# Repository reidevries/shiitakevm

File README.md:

# shiitakevm
CV-addressed multiplexor with interpolation, either for arbitrary waveshaping or crossfading ext sources
I never tested this, but have a new version in the pipeline that will hopefully be better when I test it.

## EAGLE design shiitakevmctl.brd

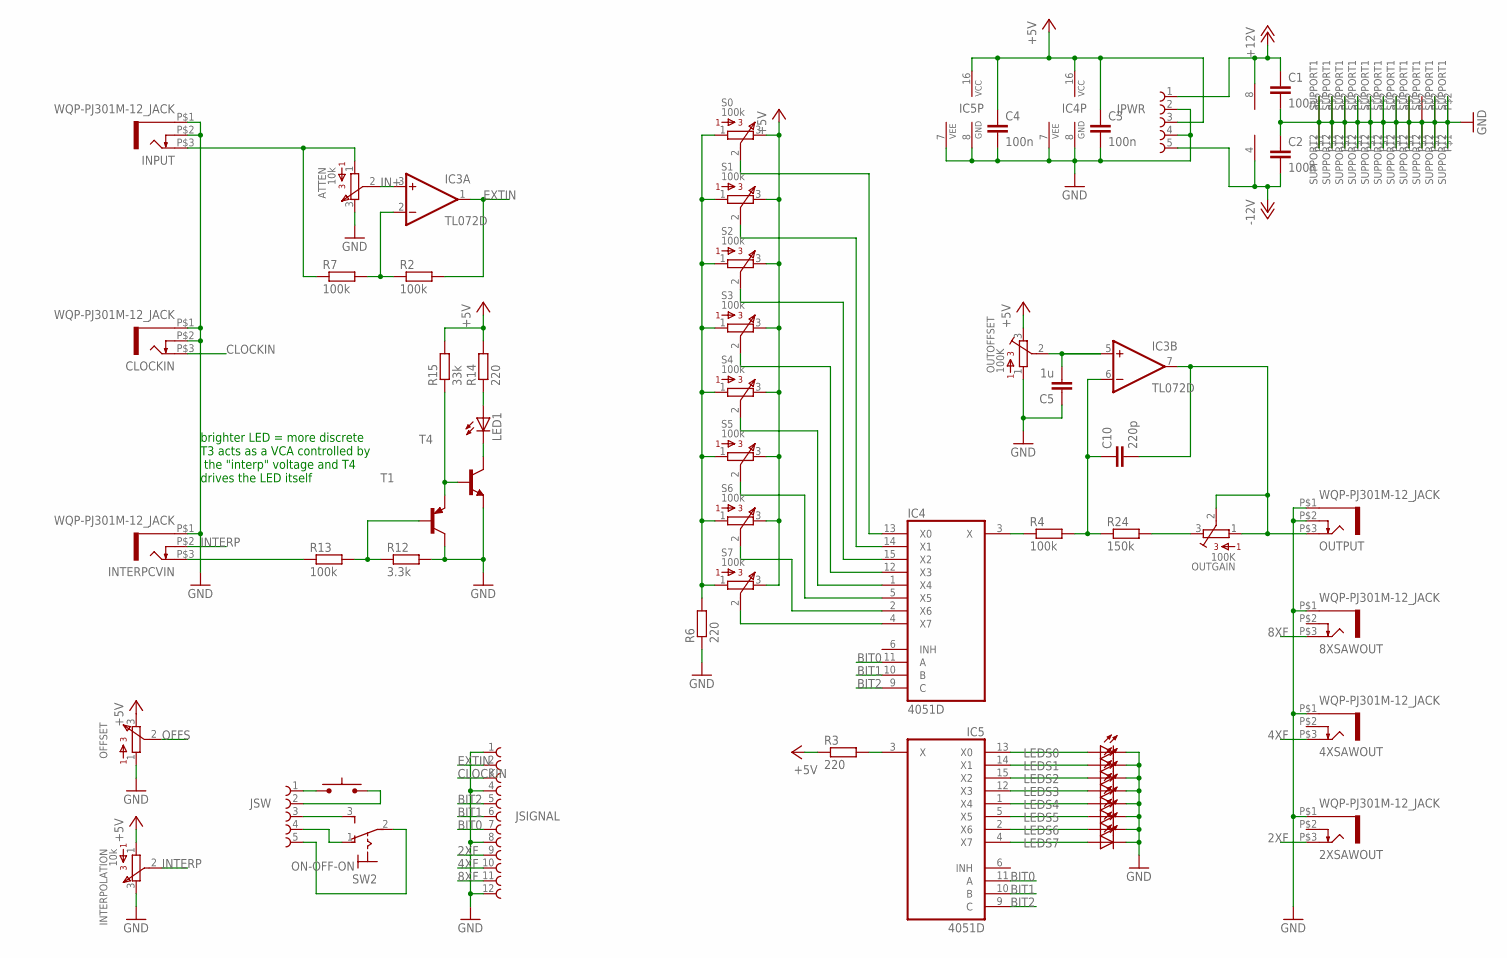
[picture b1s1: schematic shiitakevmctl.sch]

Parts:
2XSAWOUT, 4XSAWOUT, 8XSAWOUT: WQP-PJ301M-12_JACK
ATTEN: 10k; 308
C1, C2, C3, C4: 100n; C1206
C5: 1u; C1206
C10: 220p; C1206
CLOCKIN: WQP-PJ301M-12_JACK
IC3: TL072D; SO08
IC4, IC5: 4051D; SO16
INPUT: WQP-PJ301M-12_JACK
INTERPCVIN: WQP-PJ301M-12_JACK
INTERPOLATION: 10k; 308
JPWR: 61300511121
JSIGNAL: 61301211121
JSW: 61300511121
LED1: LEDCHIPLED_0805; CHIPLED_0805
LEDS0, LEDS1, LEDS2, LEDS3, LEDS4, LEDS5, LEDS6, LEDS7: LED3MM
OFFSET: 308/309; 308
OUTGAIN: 100K; 3386C
OUTOFFSET: 100K; 3386C
OUTPUT: WQP-PJ301M-12_JACK
R2, R4, R7, R13: 100k; R1206
R3, R6, R14: 220; R1206
R12: 3.3k; R1206
R15: 33k; R1206
R24: 150k; R1206
S0, S1, S2, S3, S4, S5, S6, S7: 100k; 308
SW1: PUSHSWITCH
SW2: ON-OFF-ON; 320-916
T1: MMBT3906LT1-PNP-SOT23-BEC; SOT23-BEC
T4: MMBT3904LT1-NPN-SOT23-BEC; SOT23-BEC

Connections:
2XF: 2XSAWOUT.P$3 (2), JSIGNAL.9
4XF: 4XSAWOUT.P$3 (2), JSIGNAL.10
8XF: 8XSAWOUT.P$3 (2), JSIGNAL.11
+5V: C3.1, C4.1, IC4.16 (VCC), IC5.16 (VCC), INTERPOLATION.1, JPWR.3, OFFSET.3, OUTOFFSET.3, R3.1, R14.2, R15.2, S0.3, S1.3, S2.3, S3.3, S4.3, S5.3, S6.3, S7.3
+12V: C1.1, IC3.8 (V+), JPWR.1
-12V: C2.2, IC3.4 (V-), JPWR.5
BIT0: IC4.11 (A), IC5.11 (A), JSIGNAL.7
BIT1: IC4.10 (B), IC5.10 (B), JSIGNAL.6
BIT2: IC4.9 (C), IC5.9 (C), JSIGNAL.5
CLOCKIN: CLOCKIN.P$3 (2), JSIGNAL.3
EXTIN: IC3.1 (OUT), JSIGNAL.2, R2.2
GND: 2XSAWOUT.P$1 (1), 4XSAWOUT.P$1 (1), 8XSAWOUT.P$1 (1), ATTEN.3, ATTEN.SUPPORT2, C1.2, C2.1, C3.2, C4.2, C5.1, CLOCKIN.P$1 (1), CLOCKIN.P$2 (3), IC4.7 (VEE), IC4.8 (GND), IC5.7 (VEE), IC5.8 (GND), INPUT.P$1 (1), INPUT.P$2 (3), INTERPCVIN.P$1 (1), INTERPOLATION.3, INTERPOLATION.SUPPORT1, INTERPOLATION.SUPPORT2, JPWR.2, JPWR.4, JSIGNAL.1, JSIGNAL.4, JSIGNAL.8, JSIGNAL.12, LEDS0.K (C), LEDS1.K (C), LEDS2.K (C), LEDS3.K (C), LEDS4.K (C), LEDS5.K (C), LEDS6.K (C), LEDS7.K (C), OFFSET.1, OFFSET.SUPPORT1, OFFSET.SUPPORT2, OUTOFFSET.1, OUTPUT.P$1 (1), OUTPUT.P$2 (3), R6.1, R12.2, S0.SUPPORT1, S0.SUPPORT2, S1.SUPPORT1, S1.SUPPORT2, S2.SUPPORT1, S2.SUPPORT2, S3.SUPPORT1, S3.SUPPORT2, S4.SUPPORT1, S4.SUPPORT2, S5.SUPPORT1, S5.SUPPORT2, S6.SUPPORT1, S6.SUPPORT2, S7.SUPPORT1, S7.SUPPORT2, T1.C, T4.E
IN+: ATTEN.2, IC3.3 (+IN)
INTERP: INTERPCVIN.P$2 (3), INTERPOLATION.2
unnamed: C10.1, IC3.6 (-IN), R4.2, R24.1
unnamed: C10.2, IC3.7 (OUT), OUTGAIN.1, OUTGAIN.2, OUTPUT.P$3 (2)
unnamed: ATTEN.1, INPUT.P$3 (2), R7.1
unnamed: IC4.13 (X0), S0.2
unnamed: IC4.14 (X1), S1.2
unnamed: IC4.15 (X2), S2.2
unnamed: IC4.12 (X3), S3.2
unnamed: IC4.1 (X4), S4.2
unnamed: IC4.5 (X5), S5.2
unnamed: IC4.2 (X6), S6.2
unnamed: IC4.4 (X7), S7.2
unnamed: IC4.3 (X), R4.1
unnamed: IC3.2 (-IN), R2.1, R7.2
unnamed: IC5.3 (X), R3.2
unnamed: R6.2, S0.1, S1.1, S2.1, S3.1, S4.1, S5.1, S6.1, S7.1
unnamed: R15.1, T1.E, T4.B
unnamed: LED1.C, T4.C
unnamed: R12.1, R13.2, T1.B
unnamed: INTERPCVIN.P$3 (2), R13.1
unnamed: LED1.A, R14.1
unnamed: JSW.1, SW1.P$1
unnamed: JSW.2, SW1.P$2
unnamed: JSW.4, SW2.1 (O)
unnamed: JSW.3, SW2.3 (S)
unnamed: JSW.5, SW2.2
unnamed: C5.2, IC3.5 (+IN), OUTOFFSET.2
unnamed: IC5.13 (X0), LEDS0.A
unnamed: IC5.14 (X1), LEDS1.A
unnamed: IC5.15 (X2), LEDS2.A
unnamed: IC5.12 (X3), LEDS3.A
unnamed: IC5.1 (X4), LEDS4.A
unnamed: IC5.5 (X5), LEDS5.A
unnamed: IC5.4 (X7), LEDS7.A
unnamed: IC5.2 (X6), LEDS6.A
unnamed: OUTGAIN.3, R24.2
OFFS: OFFSET.2

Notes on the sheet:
brighter LED = more discrete T3 acts as a VCA controlled by the "interp" voltage and T4 drives the LED itself

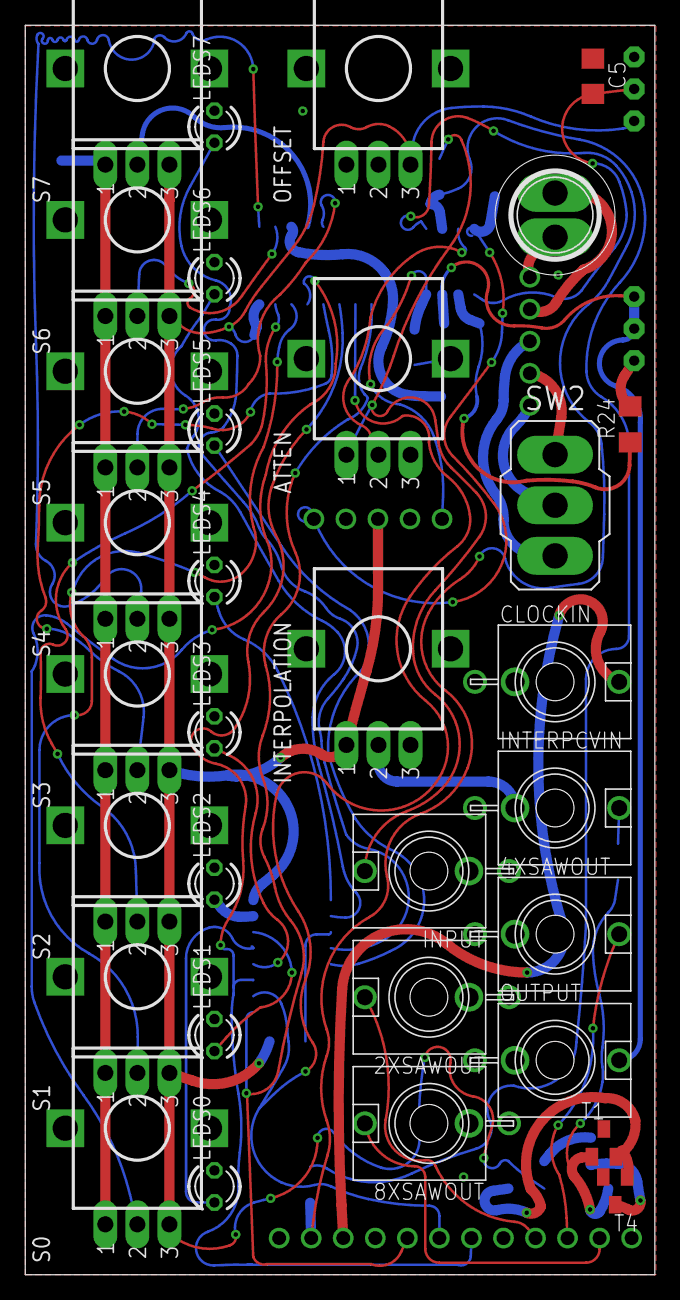
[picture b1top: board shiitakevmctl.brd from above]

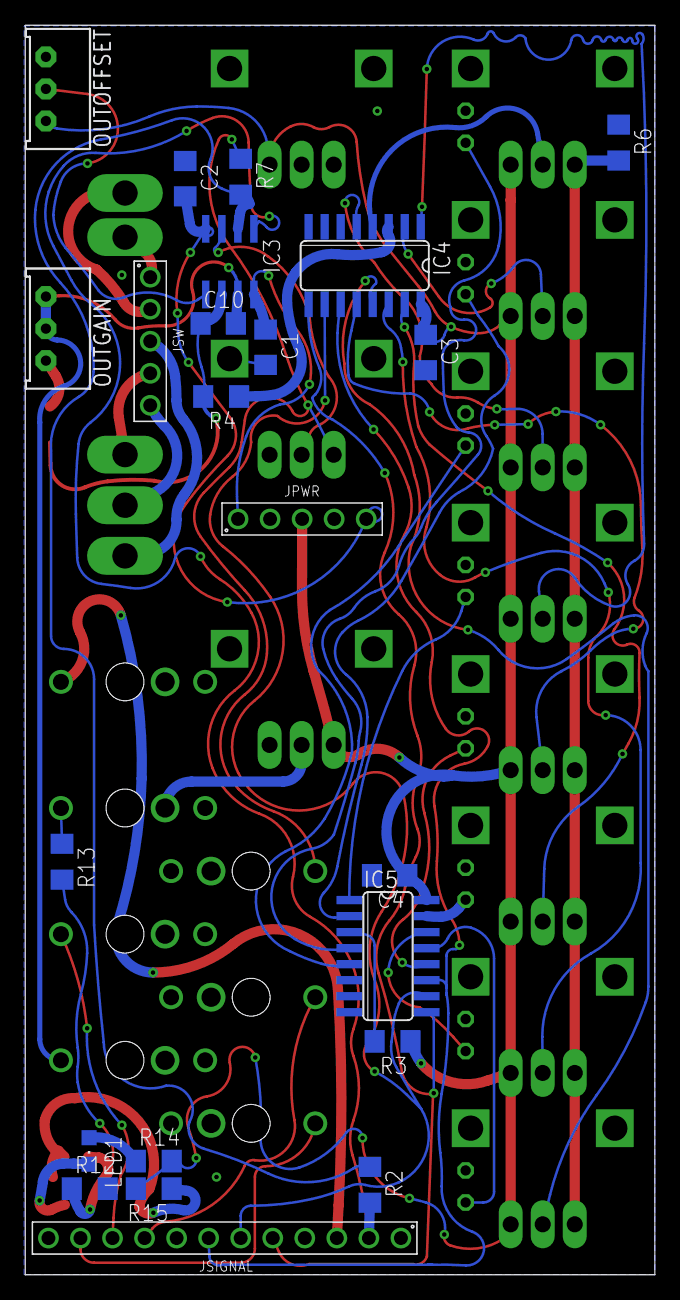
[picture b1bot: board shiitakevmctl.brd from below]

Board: 2 copper layers, 49.9 x 99.0 mm, 55 parts (23 on the bottom side), 49 nets.

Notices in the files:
parts and their libraries:
Board-to-Board: Copyright: Würth Elektronik
